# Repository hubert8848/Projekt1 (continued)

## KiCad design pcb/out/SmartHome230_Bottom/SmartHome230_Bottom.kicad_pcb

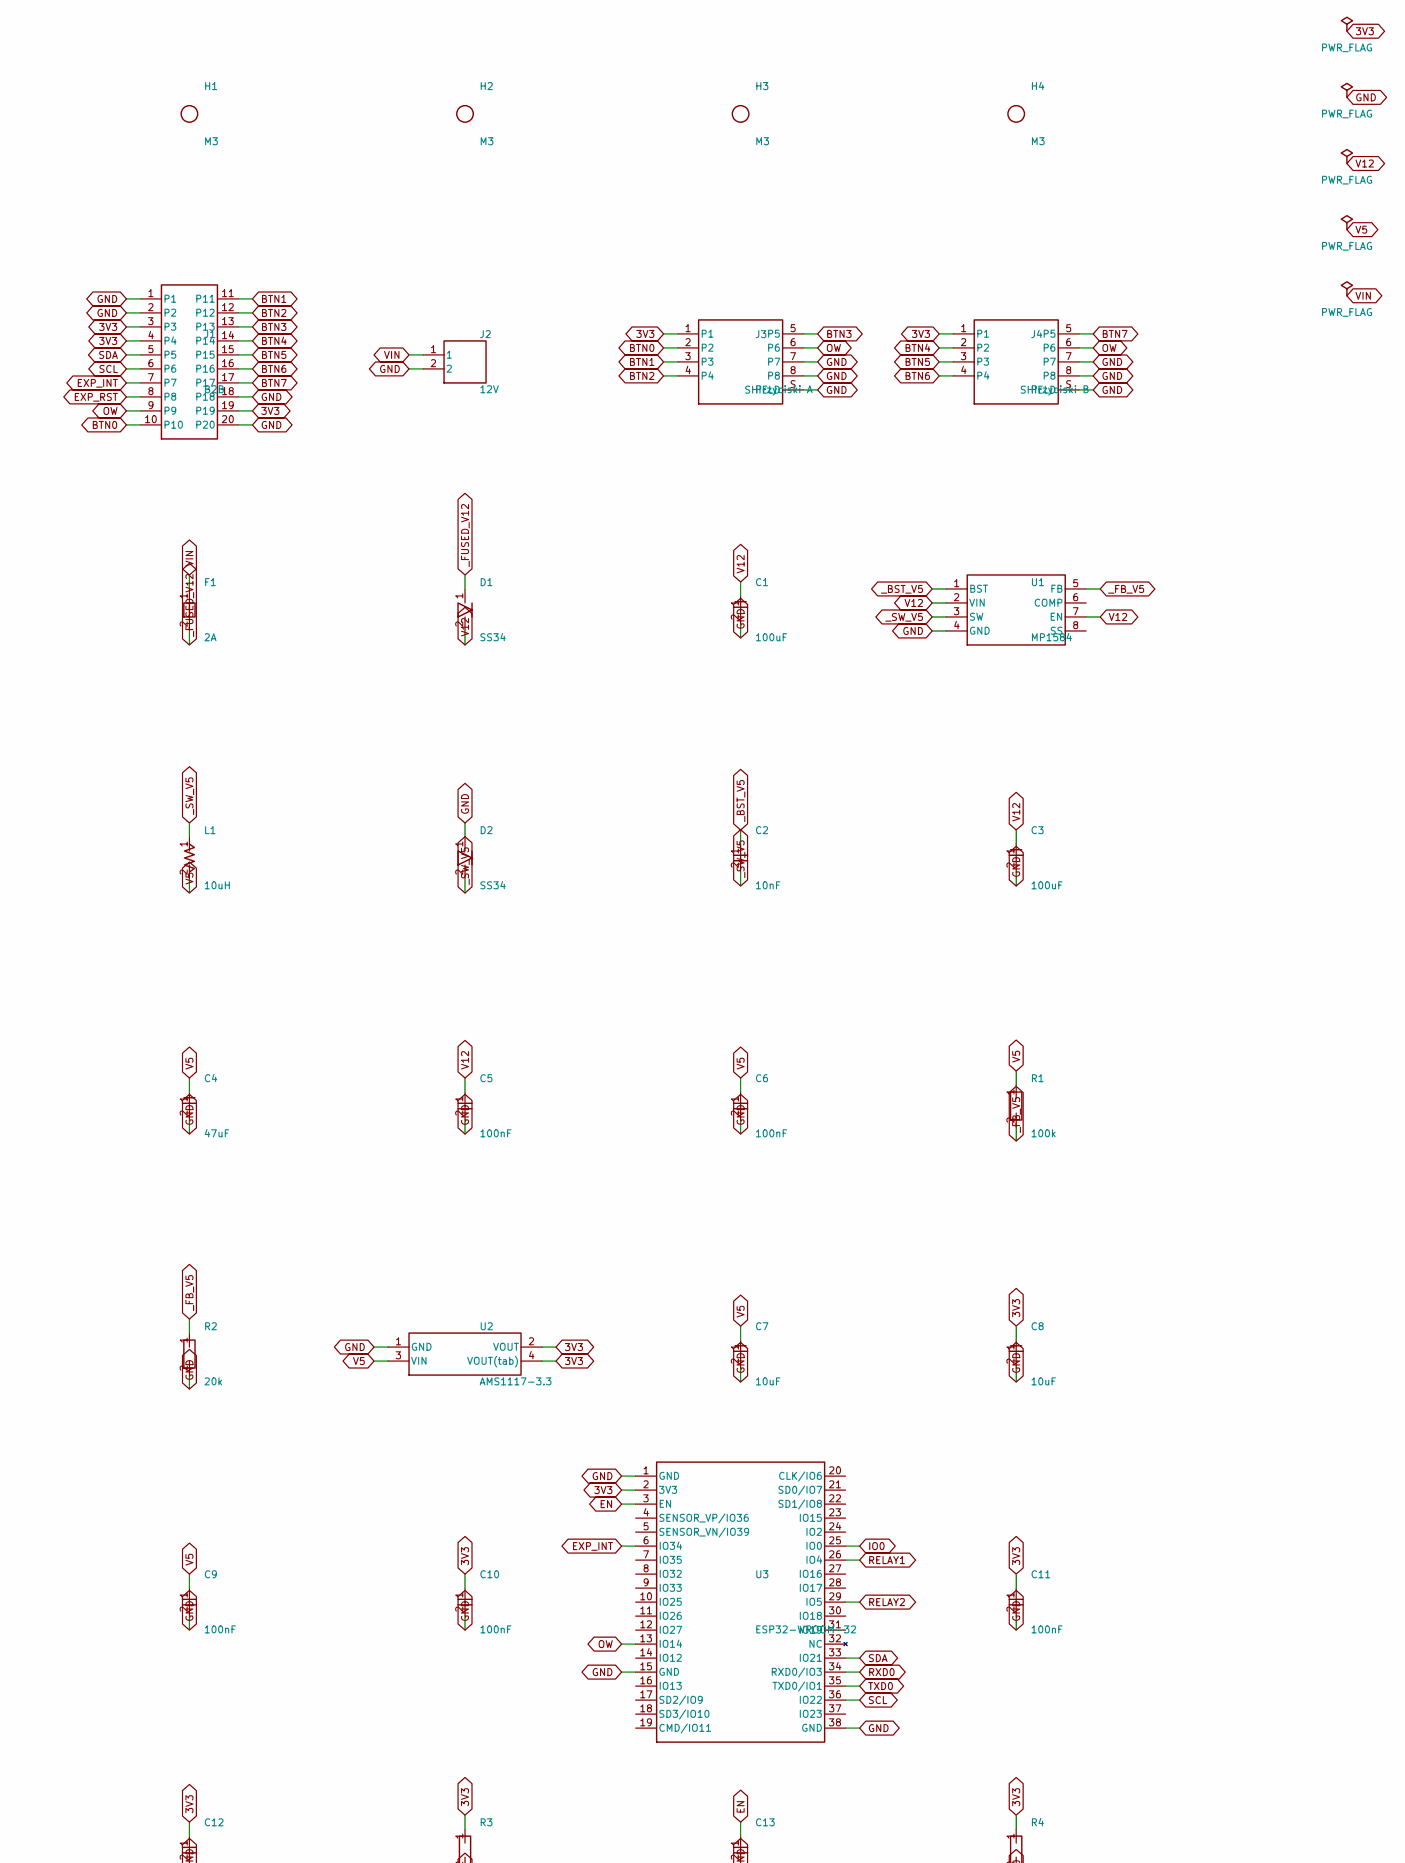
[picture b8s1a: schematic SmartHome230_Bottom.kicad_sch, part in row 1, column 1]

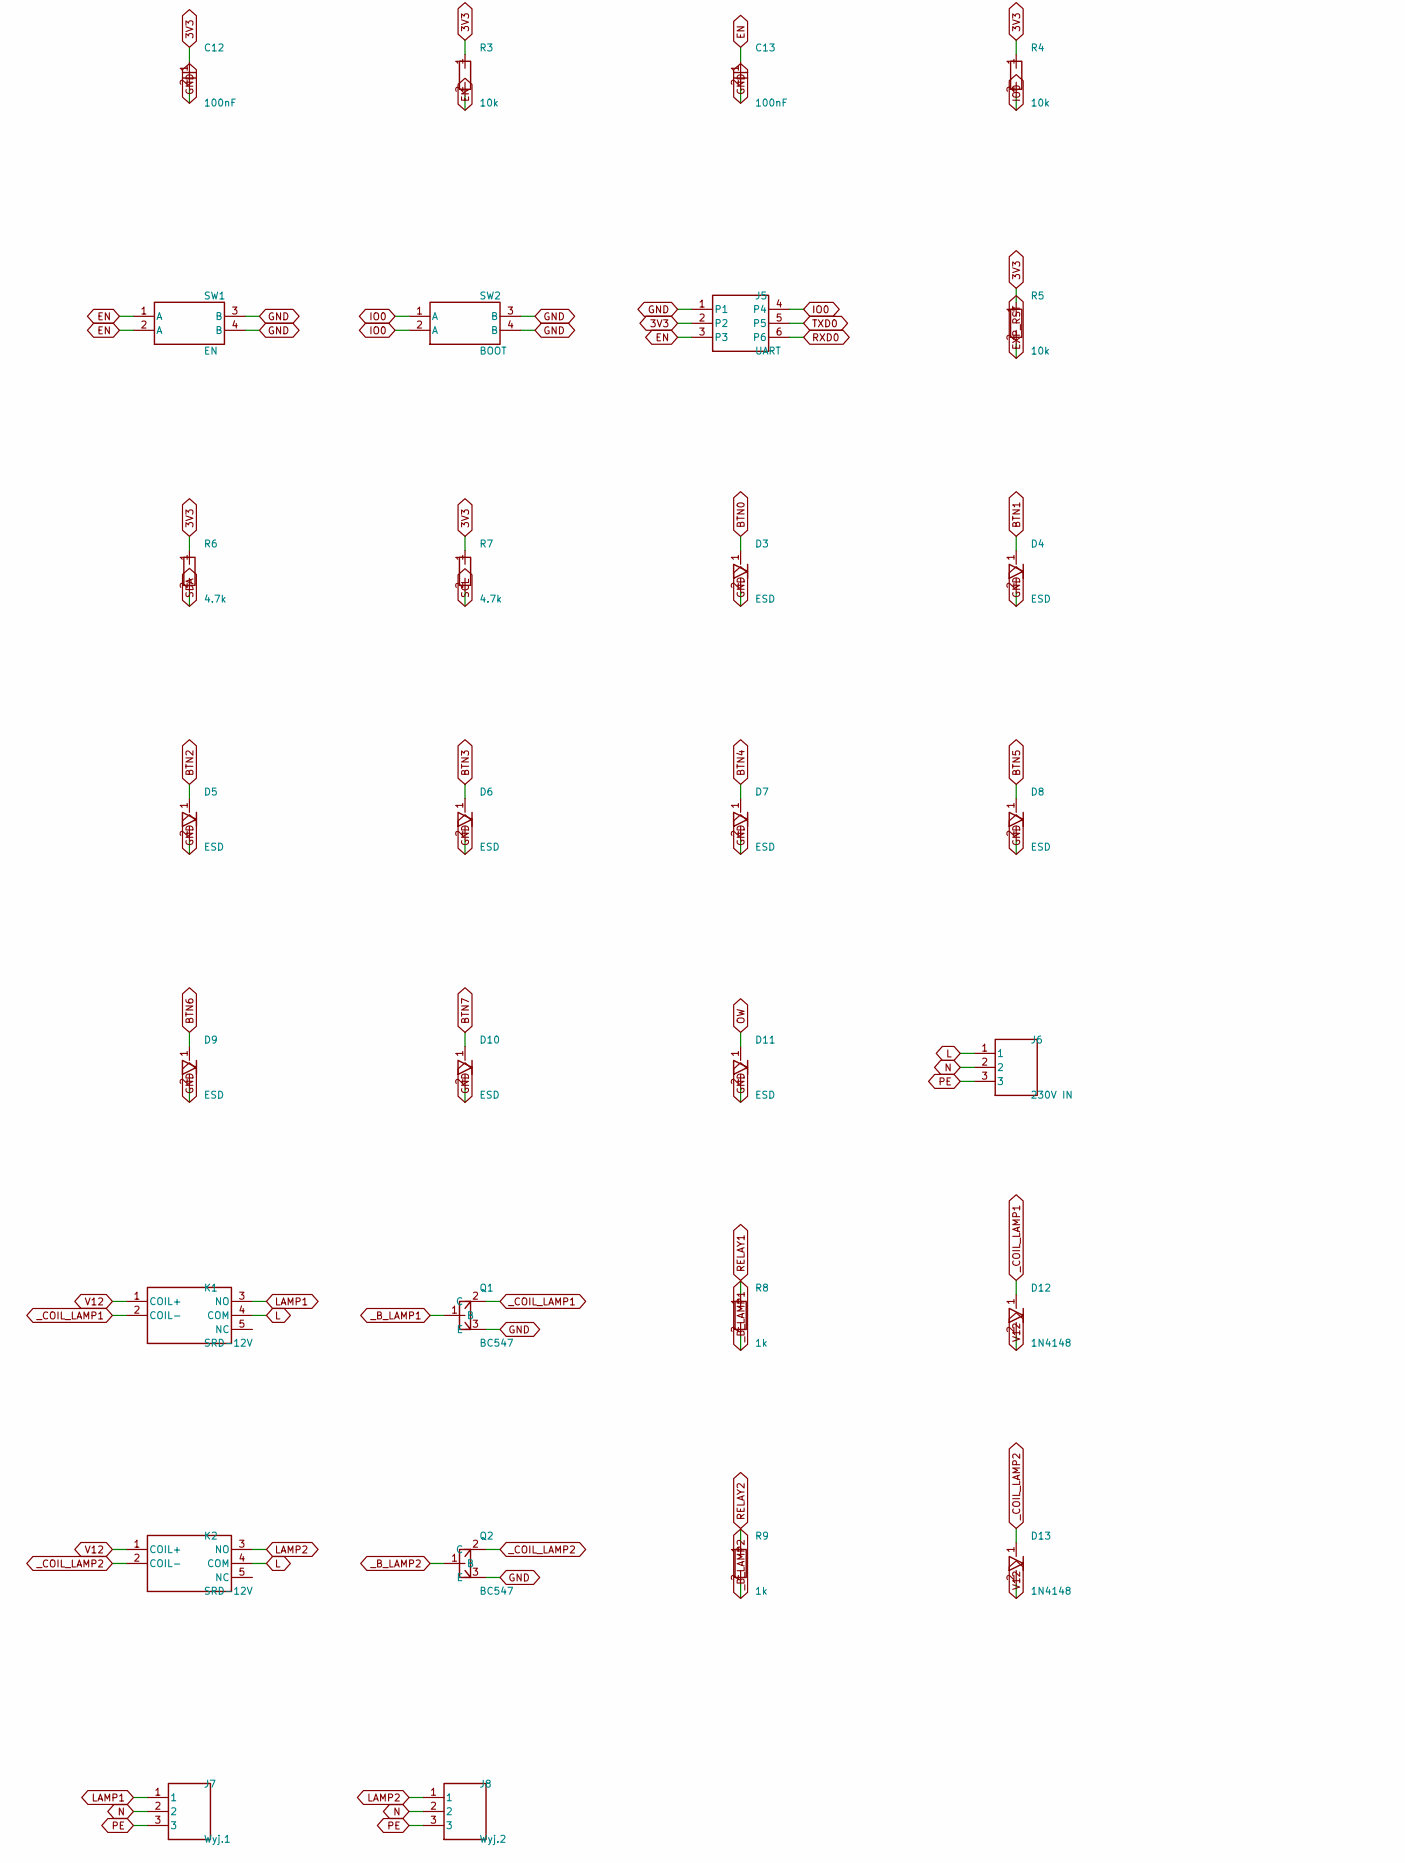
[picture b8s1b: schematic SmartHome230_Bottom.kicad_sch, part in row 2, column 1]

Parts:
C1, C3: 100uF; CP_1206
C2: 10nF; C_0805
C4: 47uF; CP_1206
C5, C6, C9, C10, C11, C12, C13: 100nF; C_0805
C7, C8: 10uF; CP_1206
D1, D2: SS34; D_SMA
D3, D4, D5, D6, D7, D8, D9, D10, D11: ESD; D_SOD-323
D12, D13: 1N4148; D_SMA
F1: 2A; F_1206
H1, H2, H3, H4: M3; MountingHole_M3
J1: B2B; Header_2x10
J2: 12V; ScrewTerminal_1x02
J3: Przyciski A; RJ45_8P8C
J4: Przyciski B; RJ45_8P8C
J5: UART; Header_1x06
J6: 230V IN; ScrewTerminal_1x03
J7: Wyj.1; ScrewTerminal_1x03
J8: Wyj.2; ScrewTerminal_1x03
K1, K2: SRD-12V; Relay_SPDT_SRD
L1: 10uH; L_6x6
Q1, Q2: BC547; SOT-23-3
R1: 100k; R_0805
R2: 20k; R_0805
R3, R4, R5: 10k; R_0805
R6, R7: 4.7k; R_0805
R8, R9: 1k; R_0805
SW1: EN; SW_Push_6mm
SW2: BOOT; SW_Push_6mm
U1: MP1584; SOIC-8
U2: AMS1117-3.3; SOT-223
U3: ESP32-WROOM-32

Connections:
3V3: C8.1, C10.1, C11.1, C12.1, J1.3, J1.4, J1.19, J3.1, J4.1, J5.2, R3.1, R4.1, R5.1, R6.1, R7.1, U2.2 (VOUT), U2.4 (VOUT(tab)), U3.2 (3V3)
BTN0: D3.1, J1.10, J3.2
BTN1: D4.1, J1.11, J3.3
BTN2: D5.1, J1.12, J3.4
BTN3: D6.1, J1.13, J3.5
BTN4: D7.1, J1.14, J4.2
BTN5: D8.1, J1.15, J4.3
BTN6: D9.1, J1.16, J4.4
BTN7: D10.1, J1.17, J4.5
EN: C13.1, J5.3, R3.2, SW1.1 (A), SW1.2 (A), U3.3 (EN)
EXP_INT: J1.7, U3.6 (IO34)
EXP_RST: J1.8, R5.2
GND: C1.2, C3.2, C4.2, C5.2, C6.2, C7.2, C8.2, C9.2, C10.2, C11.2, C12.2, C13.2, D2.1, D3.2, D4.2, D5.2, D6.2, D7.2, D8.2, D9.2, D10.2, D11.2, J1.1, J1.2, J1.18, J1.20, J2.2, J3.7, J3.8, J3.S (SHIELD), J4.7, J4.8, J4.S (SHIELD), J5.1, Q1.3 (E), Q2.3 (E), R2.2, SW1.3 (B), SW1.4 (B), SW2.3 (B), SW2.4 (B), U1.4 (GND), U2.1 (GND), U3.1 (GND), U3.15 (GND), U3.38 (GND)
IO0: J5.4, R4.2, SW2.1 (A), SW2.2 (A), U3.25 (IO0)
L: J6.1, K1.4 (COM), K2.4 (COM)
LAMP1: J7.1, K1.3 (NO)
LAMP2: J8.1, K2.3 (NO)
N: J6.2, J7.2, J8.2
OW: D11.1, J1.9, J3.6, J4.6, U3.13 (IO14)
PE: J6.3, J7.3, J8.3
RELAY1: R8.1, U3.26 (IO4)
RELAY2: R9.1, U3.29 (IO5)
RXD0: J5.6, U3.34 (RXD0/IO3)
SCL: J1.6, R7.2, U3.36 (IO22)
SDA: J1.5, R6.2, U3.33 (IO21)
TXD0: J5.5, U3.35 (TXD0/IO1)
V5: C4.1, C6.1, C7.1, C9.1, L1.2, R1.1, U2.3 (VIN)
V12: C1.1, C3.1, C5.1, D1.2, D12.2, D13.2, K1.1 (COIL+), K2.1 (COIL+), U1.2 (VIN), U1.7 (EN)
VIN: F1.1, J2.1
_BST_V5: C2.1, U1.1 (BST)
_B_LAMP1: Q1.1 (B), R8.2
_B_LAMP2: Q2.1 (B), R9.2
_COIL_LAMP1: D12.1, K1.2 (COIL-), Q1.2 (C)
_COIL_LAMP2: D13.1, K2.2 (COIL-), Q2.2 (C)
_FB_V5: R1.2, R2.1, U1.5 (FB)
_FUSED_V12: D1.1, F1.2
_SW_V5: C2.2, D2.2, L1.1, U1.3 (SW)

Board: 2 copper layers, 58 parts (0 on the bottom side), 37 nets, no tracks yet.

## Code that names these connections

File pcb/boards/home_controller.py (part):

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    # --- Gniazda RJ45: przyciski sciennie + 1-wire ---
    # RJ45 #1: 3V3, BTN0..3, OW, GND, GND
    j2 = d.add(Component("J2", "RJ45", "RJ45-A", "RJ45_8P8C"))
    for pin, net in zip("12345678", ["3V3", "BTN0", "BTN1", "BTN2", "BTN3", "OW", "GND", "GND"]):
        j2.connect(pin, net)
    j2.connect("S", "GND")
    # RJ45 #2: 3V3, BTN4..7, OW, GND, GND
    j3 = d.add(Component("J3", "RJ45", "RJ45-B", "RJ45_8P8C"))
    for pin, net in zip("12345678", ["3V3", "BTN4", "BTN5", "BTN6", "BTN7", "OW", "GND", "GND"]):
        j3.connect(pin, net)
    j3.connect("S", "GND")
    # RJ45 #3: 3V3, BTN8..11, OW, GND, GND
    j4 = d.add(Component("J4", "RJ45", "RJ45-C", "RJ45_8P8C"))
    for pin, net in zip("12345678", ["3V3", "BTN8", "BTN9", "BTN10", "BTN11", "OW", "GND", "GND"]):
        j4.connect(pin, net)
    j4.connect("S", "GND")
    # RJ45 #4: 3V3, BTN12..15, OW, GND, GND
    j5 = d.add(Component("J5", "RJ45", "RJ45-D", "RJ45_8P8C"))
    for pin, net in zip("12345678", ["3V3", "BTN12", "BTN13", "BTN14", "BTN15", "OW", "GND", "GND"]):
        j5.connect(pin, net)
    j5.connect("S", "GND")

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
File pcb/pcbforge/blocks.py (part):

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
    def tft_connector(self, p3v3, gnd, label="TFT"):
        """Zlacze wyswietlacza TFT SPI dotykowego (1x14)."""
        pins = {"1": gnd, "2": p3v3, "3": "TFT_CS", "4": "TFT_RST", "5": "TFT_DC",
                "6": "SPI_MOSI", "7": "SPI_SCK", "8": p3v3, "9": "SPI_MISO",
                "10": "TOUCH_CS", "11": "TOUCH_IRQ", "12": "SPI_MISO", "13": gnd, "14": p3v3}
        self.add("J", "Header_2x07", label, pins, role="io", label="Ekran TFT dotykowy")
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
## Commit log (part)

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2025-06-19 Add snooze feature
